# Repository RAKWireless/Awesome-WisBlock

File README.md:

# Welcome to _**Awesome WisBlock**_ 

[RAKwireless WisBlock](https://docs.rakwireless.com/Product-Categories/WisBlock/) is open source. Not only the software is open source, but the hardware is as well.

### NEW
We shared now our latest enclosure designs and accessories in [MakerWorld](https://makerworld.com/en/collections/8038419-rakwireless-origins), [Printables](https://www.printables.com/@BerndGieseck_3488104/models) and [Thingiverse](https://www.thingiverse.com/beegee1962/collections/29065520/things).
Check out our shares in [Shared-3D-For-Printing](./Shared-3D-For-Printing/Shared-3D-Print-Examples.md)

To support you, we created the _**Awesome WisBlock**_ repository. Here you find 
- tutorials how to create your own **WisBlock Sensor** or **WisBlock IO** modules
- 3D printable enclosures
- 3D printable mounting plates for our **WisBlock Unified Enclosures**

<center></center>     

----

<center></center>

**Content**    
- [WisBlock modules](./WisBlock-Modules/README.md)
- [3D printable enclosures](./Enclosures/README.md)
- [Unify Enclosure Mounting Plates](./Unify-Enclosure/README.md)

----

----

Thank you for sharing your _**awesome**_ creation here and supporting RAKwireless by using our WisBlock products.    

**RAKwireless invests time and resources providing this open source code, please support RAKwireless and open-source hardware by purchasing products from [RAKwireless](https://rakwireless.com/)!**

_**For support and questions about RAKwireless products please visit our [forum](https://forum.rakwireless.com/)**_    
_**For examples and quick start tutorial please visit our [Github Repo](https://github.com/RAKWireless/Wisblock)**_    
_**For additional information about RAK products please visit our [Documentation Center](https://docs.rakwireless.com/) and our [Knowledge Hub](https://docs.rakwireless.com/Knowledge-Hub/Learn/)**_    
_**To buy WisBlock modules please visit our [online store](https://store.rakwireless.com/)**_

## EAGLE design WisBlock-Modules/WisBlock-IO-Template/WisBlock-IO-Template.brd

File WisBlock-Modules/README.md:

# Welcome to _**Awesome WisBlock Modules**_ 

[RAKwireless WisBlock](https://docs.rakwireless.com/Product-Categories/WisBlock/) is open source. Not only the software is open source, but the hardware is as well.

To support you, we created the _**Awesome WisBlock**_ repository. Here you find tutorials how to create your own **WisBlock Sensor** or **WisBlock IO** modules.    

<center></center>     

If you have created your own awesome IO or Sensor module, please share it here with the **WisBlock** community and become a **RAKstar**. And if it is something real awesome, **RAKwireless** might even produce it.

----

<center></center>

**Content**
- [Read this first](#read-this-first)
- [WisBlock Sensor tutorial](#wisblock-sensor-tutorial)
- [WisBlock IO tutorial](#wisblock-io-tutorial)
- [Board-to-boardconnectors](#board-to-board-connectors)
   - [Connector data sheets](#connector-data-sheets)
   - [Connector part library](#connector-part-library)
- [RAK examples](#rak-examples)
   - [RTC example](#rtc-example)
   - [IO extender example](#io-extender-example)
- [Community created modules](#community-created-modules)
   - [WisBlock SDI12 Module](../WisBlock-Modules/WisBlock-IO-Modules/WisBlock-SDI12-Module)

----

## Read this first
- The board-to-board connectors used in the **WisBlock** products can be bought from the [RAKwireless store](https://store.rakwireless.com). There are two suppliers for the connectors, Panasonic and TXGA. On the base board (RAK19007) are the female/socket version, on the modules are the male/header version      
- Have a good look into the datasheet of the **RAK19007 WisBlock Base** board to understand the signals connected to the 4 sensor slots. => [RAK19007 datasheet](https://docs.rakwireless.com/product-categories/wisblock/rak19007/datasheet/)    
- Have a good look into the datasheet of one of the existing **WisBlock Sensor** modules to understand the usage of the signals. For example the [RAK1906 Environment sensor](https://docs.rakwireless.com/product-categories/wisblock/rak1906/datasheet/rak1906/datasheet/)    
- Have a good look into the datasheet of one of the existing **WisBlock IO** modules to understand the usage of the signals. For example the [RAK1920 Sensor Adapter](https://docs.rakwireless.com/product-categories/wisblock/rak1906/datasheet/rak1920/datasheet/)    

----

## WisBlock Sensor tutorial
This tutorial leads you throught the steps to create your own **WisBlock Sensor** module. You can find the step-by-step tutorial _**[here](../WisBlock-Modules/WisBlockSensorTutorial.md)**_    
To make the task easier, we have prepared a complete example project for Autodesk Eagle™. You can download it [here](../WisBlock-Modules/WisBlock-Sensor-Template.zip).

## WisBlock IO tutorial
This tutorial leads you throught the steps to create your own **WisBlock IO** module. You can find the step-by-step tutorial _**[here](../WisBlock-Modules/WisBlockIOTutorial.md)**_    
To make the task easier, we have prepared a complete example project for Autodesk Eagle™. You can download it [here](../WisBlock-Modules/WisBlock-IO-Template.zip).    

Thanks to RAKstar psupine we have now the example project for KiCad. Thank you very much for your contribution. You can download the [KiCad project here](./WisBlock-IO-Template-KiCad.zip)

Thanks to RAKstar @antoniovalente we have as well an SDI12 module available.

## Board-to-board connectors
⚠️ The TXGA connector is no longer available. Compatible parts are available from Panasonic and BOX

| 24 Pin Male | 24 Pin Female |
| :--: | :--: |
|  |  |     

The board-to-board connectors used in the WisBlock products can be bought from the [RAKwireless store](https://store.rakwireless.com). There are two suppliers for the connectors, Panasonic and BOX. On the base board (RAK19007) are the female/socket version, on the modules are the male/header version.      
There are two types of connectors. The 24pin male connector is used for WisBlock Sensor modules. The 40pin male connector is used for WisBlock IO modules.    
| 40 Pin Male | 40 Pin Female |
| :--: | :--: |
|  |  |    

### Connector data sheets
   - Panasonic connector [data sheet](https://industry.panasonic.eu/productfinder?search=AXE6&op=Find+your+product&mode=SEARCH_MODE&rangeAttributeFilters=%5B%5D&sort=%2Casc&attributeFilters=product_state%3Anew%2Cactive)    
   - BOX connector [product page](http://www.boxgroup.hk/)    

### Connector part library
Due to strict rules of [Component Search Engine](https://componentsearchengine.com) we cannot offer the ready to use libraries for download.  
  
You can get the libraries from these links, but you will have to register at _Component Search Engine_ to do so.  

Link to [24 pin Connector for Sensor Slot](https://componentsearchengine.com/part.php?partID=12868517)    
     
Link to [40 pin Connector for IO Slot](https://componentsearchengine.com/part.php?partID=12868607) 

## RAK examples
We prepared a custom **WisBlock Sensor** and a custom **WisBlock IO** module as ready to go Eagle™ projects.

### RTC example
This Eagle™ project is the outcome of the **WisBlock Sensor** tutorial. It is a RTC module with integrated backup battery.

### IO extender example
This Eagle™ project is the outcome of the **WisBlock IO** tutorial. It is an IO extender that gives you access to more GPIO's.

## Community created modules
This is your space. We hope that you share the _**awesome**_ **WisBlock Sensor** and **WisBlock IO** you created here with the community.    

----
### Mini IO extender 10x23mm footprint
https://github.com/piecol/Wisblock_IO_extention_10x23/

### WisBlock Power Module Template
https://github.com/piecol/WisBlock_Power_module_template

----

Thank you for sharing your _**awesome**_ creation here and supporting RAKwireless by using our WisBlock products.    

**RAKwireless invests time and resources providing this open source code, please support RAKwireless and open-source hardware by purchasing products from [RAKwireless](https://rakwireless.com/)!**

_**For support and questions about RAKwireless products please visit our [forum](https://forum.rakwireless.com/)**_    
_**For examples and quick start tutorial please visit our [Github Repo](https://github.com/RAKWireless/Wisblock)**_    
_**For additional information about RAK products please visit our [Documentation Center](https://docs.rakwireless.com/) and our [Knowledge Hub](https://docs.rakwireless.com/Knowledge-Hub/Learn/)**_    
_**To buy WisBlock modules please visit our [online store](https://store.rakwireless.com/)**_

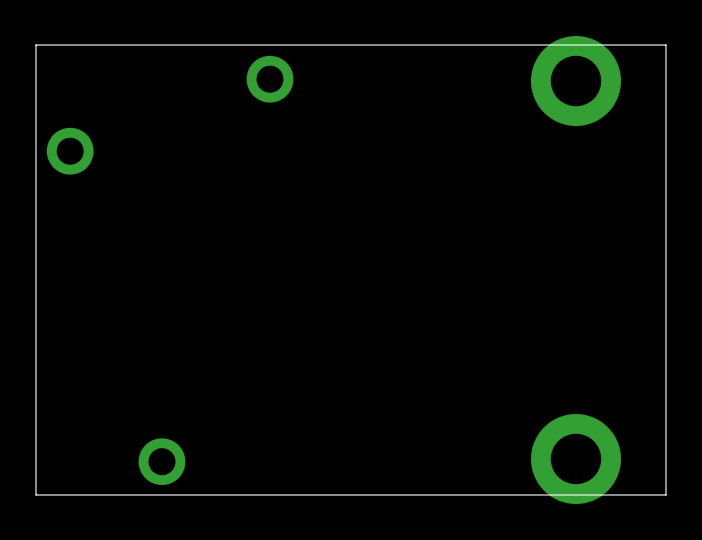
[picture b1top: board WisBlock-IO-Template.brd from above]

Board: 2 copper layers, 35.0 x 25.0 mm, 7 parts (1 on the bottom side), 3 nets, no tracks yet.

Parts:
J1: FBB04004-M40S1003K6M; FBB04004M40S1003K6M
U$1: RAK_LOGO; WISBLOCK_LOGO
U$2, U$3: RAK_IO_FIX_LARGE
U$4, U$5, U$6: RAK_IO_FIX_SMALL

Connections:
GND: J1.3, J1.4, J1.39, J1.40, J1.MP1, J1.MP2, J1.MP3, J1.MP4
VBAT: J1.1, J1.2
VDD: J1.17, J1.18

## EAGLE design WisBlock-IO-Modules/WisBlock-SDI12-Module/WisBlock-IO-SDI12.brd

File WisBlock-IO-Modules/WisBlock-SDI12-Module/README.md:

# WisBlock IO - SDI-12 Module

This module was created to connect to **SDI-12 sensors**. 

Many of the sensors used in agriculture use the SDI-12 communication protocol. The protocol uses only three lines, two supply and one, bi-directional, for data communication in a master-slave mode (the sensor element is slave). More details of the protocol [here](http://www.sdi-12.org/).

## SDI-12 block

The SDI-12 block is composed of a single inverting buffer driver ([74LVC1G240](https://www.ti.com/product/SN74LVC1G240)) with 3-state output to send data from the WisBlock serial port (`TXD1`). Data them goes throught a protection block a reaches the SDI12 data line (`SDI12_DATA`). Data from SDI12 data line, after pass the protection block, is inverted and level shifted by a simple MOSFET and feeds the serial port (`RXD1`).

<center></center>

The port pins used are:
| WisBlock IO connector PIN | Meaning |
| :--: | :--: |
| `TXD1` | Serial Port TxD data |
| `RXD1` | Serial Port RxD data |
| `IO4`  | Trasmition/Reception Selector |

## 5V DC-DC Converter

Although in the protocol the supply is 12V, most sensors used in agriculture work with a 5V supply (eg the [Meter Group](https://www.metergroup.com/environment/products/)'s ATMOS, TEROS and ECHO20 sensors). Thus, the design solution was to implement a 5V DC/DC converter with extremely low quiescent current consumption ([ISL9122A](https://www.renesas.com/in/en/products/power-management/switching-regulators/integrated-fet-regulators/device/ISL9122A.html) from Renesas). 

<center></center>

The port pins used are:
| WisBlock IO connector PIN | Meaning |
| :--: | :--: |
| `I2C1_SDA` | I2C SDA pin |
| `I2C1_SCL` | I2C SCL pin |
| `IO5`  | Enable/Disable 5V |

## 18-bit ADC

An 18-bit analog channel ([MCP3421](https://www.microchip.com/wwwproducts/en/en520011) from Microchip) for sensors such as Irrometer's [Watermark](https://www.irrometer.com/sensors.html#wm) and PinoTech's [SoilWatch 10](https://pino-tech.eu/soilwatch10/) has also included.

<center></center>

The port pins used are:
| WisBlock IO connector PIN | Meaning |
| :--: | :--: |
| `I2C1_SDA` | I2C SDA pin |
| `I2C1_SCL` | I2C SCL pin |

## Important Remarks

The module 3V3 power is from the WisBlock switched power, `3V3_S`, to power off the module for low power comsumption. Also, the used DC/DC converter has extremely low quiescent current consumption and can be shutdown by the WisBlock pin (`IO5`) - same pin used in the RAK1920 IO module for shutdown the 5V DC/DC conveter.

The used DC/DC convert has three operation modes:
| Operation Mode | Habilitation | Quiescent Current Consumption |
| :--: | :--: | :--: |
| Regulation | EN=1 or `IO5`=1 | 1300 nA |
| Forced Bypass | I2C selected | 120nA  |
| Shutdown | EN=0 or `IO5`=0 | 8 nA |

 ## WisBlock IO SDI-12 PCB
| TOP | BOTTOM |
| :--: | :--: |
|  |  |

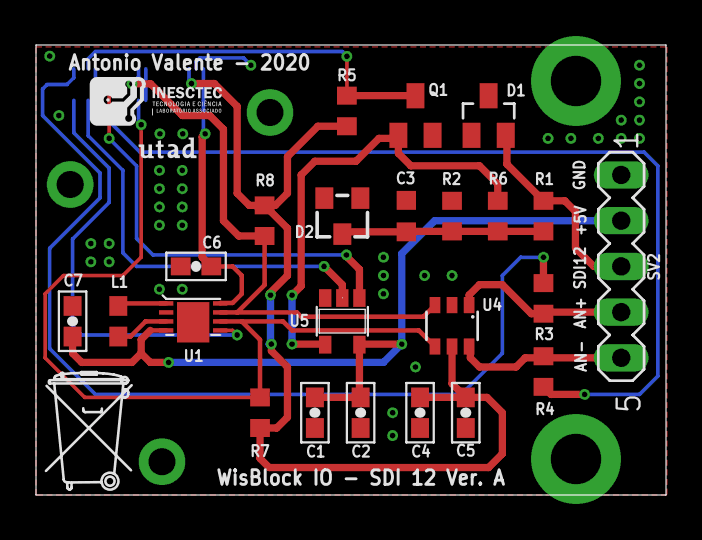
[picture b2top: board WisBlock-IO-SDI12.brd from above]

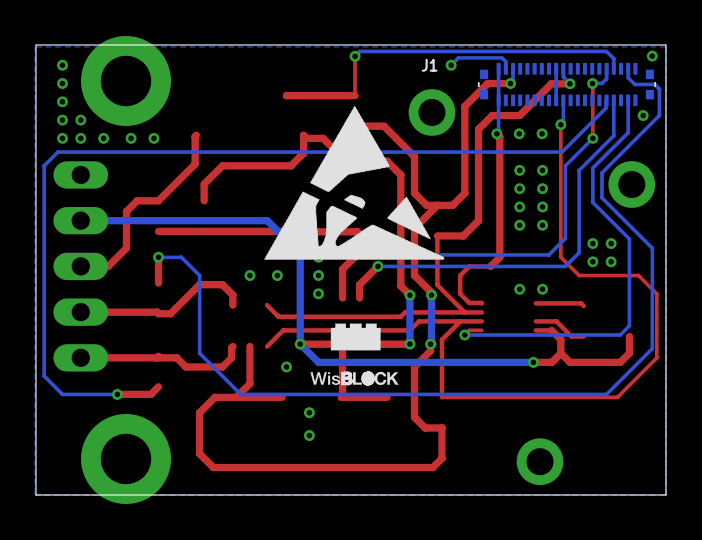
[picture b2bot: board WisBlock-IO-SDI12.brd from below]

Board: 2 copper layers, 35.0 x 25.0 mm, 34 parts (2 on the bottom side), 20 nets.

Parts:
C1, C4: 100nF; SCHMALZHAUS_0603-CAP
C2, C5, C6, C7: 10uF; SCHMALZHAUS_0603-CAP
C3: 3.3nF; C0603K
D1: CDSOT23-SMT12; SOT23
D2: BZX84CSMD; TO236
J1: FBB04004-M40S1003K6M; FBB04004M40S1003K6M
L1: 1uH; 0603
Q1: BSS123; SOT23
R1, R6: 510R; R0603
R2: 220k; R0603
R3: 7.5k; R0603
R4: 0R; R0603
R5: 47k; R0603
R7, R8: 4.7k; R0603
SV2: MA05-1
U1: ISL9122A; 8-DFN
U4: MCP3421; SOT23-6
U5: 74LVC1G240DCK; SOT23-5
U$1: RAK_LOGO; WISBLOCK_LOGO
U$2, U$3: RAK_IO_FIX_LARGE
U$4, U$5, U$6: RAK_IO_FIX_SMALL
U$7: INESCTEC_5MM
U$8: UTAD_NEW_5MM
U$9: TONNE_10.00
U$10: ESD_10.00

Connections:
3V3_S: C4.1, C5.1, J1.6, R5.2, R7.2, R8.2, U4.5
+5V: C1.1, C2.1, C7.1, SV2.2, U1.4, U5.5
AN+: R3.2, SV2.4, U4.1
AN-: R4.2, SV2.5, U4.6
GND: C1.2, C2.2, C3.2, C4.2, C5.2, C6.2, C7.2, D1.3, D2.A, J1.3, J1.4, J1.39, J1.40, J1.MP1, J1.MP2, J1.MP3, J1.MP4, Q1.2, R2.1, SV2.1, U1.2, U1.PAD, U4.2, U5.3
I2C1_SCL: J1.20, R8.1, U1.7, U4.3
I2C1_SDA: J1.19, R7.1, U1.6, U4.4
IO3: J1.31, R4.1
IO4: J1.32, U5.1
IO5: J1.37, U1.5
IO6: J1.38, R3.1
unnamed: C3.1, D2.C, R1.2, R2.2, R6.1
unnamed: L1.1, U1.3
unnamed: L1.2, U1.1
unnamed: Q1.1, R6.2, U5.4
RXD1: J1.34, Q1.3, R5.1
SDI12_DATA: D1.2, R1.1, SV2.3
TXD1: J1.33, U5.2
VBAT: C6.1, J1.1, J1.2, U1.8
VDD: J1.17, J1.18

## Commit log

2020-10-13 Add content
2020-10-13 Fix README.md
2020-10-13 Added WisBlock IO module tutorial and example files
2020-10-13 Fix typo
2020-11-13 Add 3D printable enclosures
2020-11-13 Fix links
2020-11-13 Update following the review input
2020-11-16 Add missing WisBlock 3D files
2020-11-28 Created
2020-11-28 Upadated images and links
2020-11-28 Updated README and images uploaded
2020-12-30 Fix Connector orientation
2021-01-02 Correct position of mounting holes in IO module
2021-01-22 Fix wrong net name in Sensor template
2021-03-03 Remove connector libraries due to share restrictrions
2021-03-12 Thanks to RAKstar _**psupine**_ we have now the example project for KiCad. Thank you very much for your contribution.
2021-11-05 Update License
2022-02-27 Add new indoor enclosure idea.
2022-02-27 Fix images for new enclosure
2022-03-28 Restructure and add Unified Enclosures
2022-03-28 Ass empty medium mounting plate
2022-07-22 Add more Unfify Enclosure stuff
2022-07-22 Add battery holder for Unify
2023-06-17 Update README.md
    Add Mini IO extender
2023-06-17 Update README.md
    Add RAK19001
2023-06-18 Added link to files
2023-06-18 Update README.md
    add wisblock power module template
2023-07-23 Add outdoor PoC for Unify Enclosures Add indoor PoC for air quality sensor RAK10702
2023-07-23 Add video
2023-07-23 Correct wrong link
2023-07-23 Fix the mess
2023-07-23 Fix images
2025-05-12 Update connector links
2025-07-31 Ass links for shared designs in MakerWorld, Printable and Thingiverse

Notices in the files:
parts and their libraries:
SparkFun-Coils: Licensing: Creative Commons ShareAlike 4.0 International - https://creativecommons.org/licenses/by-sa/4.0
